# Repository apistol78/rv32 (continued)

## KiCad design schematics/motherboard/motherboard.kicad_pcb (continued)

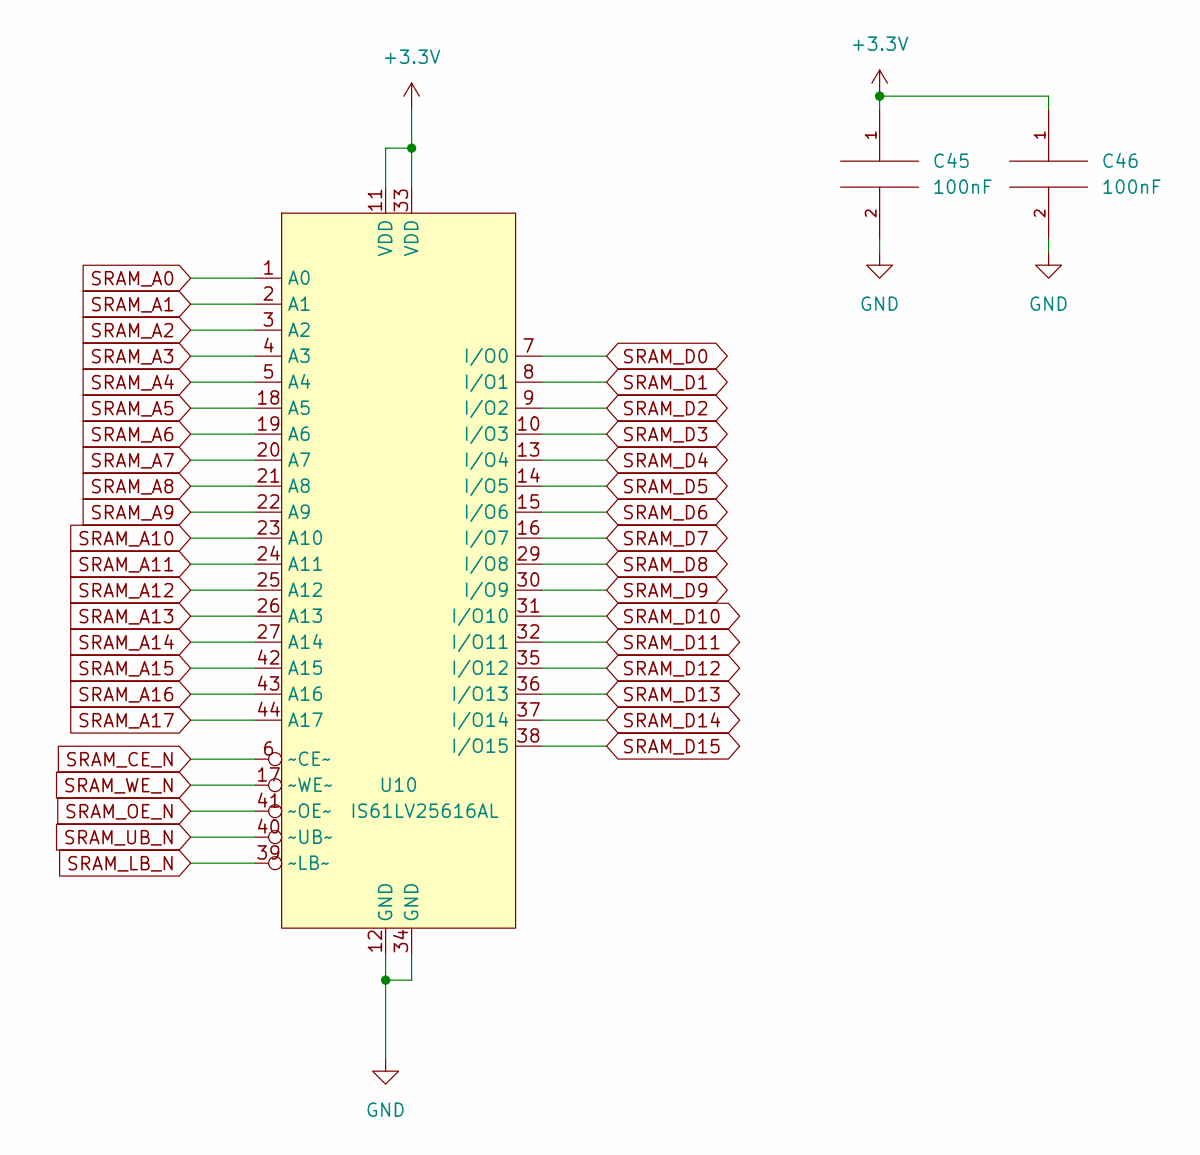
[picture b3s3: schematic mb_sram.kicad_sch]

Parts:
C45, C46: 100nF; C_0805_2012Metric_Pad1.18x1.45mm_HandSolder
U10: IS61LV25616AL; TSOP-II-44_10.16x18.41mm_P0.8mm

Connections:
+3V3: C45.1, C46.1, U10.11 (VDD), U10.33 (VDD); also elsewhere on the board
GND: C45.2, C46.2, U10.12 (GND), U10.34 (GND); also elsewhere on the board
SRAM_A0: U10.1 (A0); also elsewhere on the board
SRAM_A1: U10.2 (A1); also elsewhere on the board
SRAM_A2: U10.3 (A2); also elsewhere on the board
SRAM_A3: U10.4 (A3); also elsewhere on the board
SRAM_A4: U10.5 (A4); also elsewhere on the board
SRAM_A5: U10.18 (A5); also elsewhere on the board
SRAM_A6: U10.19 (A6); also elsewhere on the board
SRAM_A7: U10.20 (A7); also elsewhere on the board
SRAM_A8: U10.21 (A8); also elsewhere on the board
SRAM_A9: U10.22 (A9); also elsewhere on the board
SRAM_A10: U10.23 (A10); also elsewhere on the board
SRAM_A11: U10.24 (A11); also elsewhere on the board
SRAM_A12: U10.25 (A12); also elsewhere on the board
SRAM_A13: U10.26 (A13); also elsewhere on the board
SRAM_A14: U10.27 (A14); also elsewhere on the board
SRAM_A15: U10.42 (A15); also elsewhere on the board
SRAM_A16: U10.43 (A16); also elsewhere on the board
SRAM_A17: U10.44 (A17); also elsewhere on the board
SRAM_CE_N: U10.6 (~CE~); also elsewhere on the board
SRAM_D0: U10.7 (I/O0); also elsewhere on the board
SRAM_D1: U10.8 (I/O1); also elsewhere on the board
SRAM_D2: U10.9 (I/O2); also elsewhere on the board
SRAM_D3: U10.10 (I/O3); also elsewhere on the board
SRAM_D4: U10.13 (I/O4); also elsewhere on the board
SRAM_D5: U10.14 (I/O5); also elsewhere on the board
SRAM_D6: U10.15 (I/O6); also elsewhere on the board
SRAM_D7: U10.16 (I/O7); also elsewhere on the board
SRAM_D8: U10.29 (I/O8); also elsewhere on the board
SRAM_D9: U10.30 (I/O9); also elsewhere on the board
SRAM_D10: U10.31 (I/O10); also elsewhere on the board
SRAM_D11: U10.32 (I/O11); also elsewhere on the board
SRAM_D12: U10.35 (I/O12); also elsewhere on the board
SRAM_D13: U10.36 (I/O13); also elsewhere on the board
SRAM_D14: U10.37 (I/O14); also elsewhere on the board
SRAM_D15: U10.38 (I/O15); also elsewhere on the board
SRAM_LB_N: U10.39 (~LB~); also elsewhere on the board
SRAM_OE_N: U10.41 (~OE~); also elsewhere on the board
SRAM_UB_N: U10.40 (~UB~); also elsewhere on the board
SRAM_WE_N: U10.17 (~WE~); also elsewhere on the board

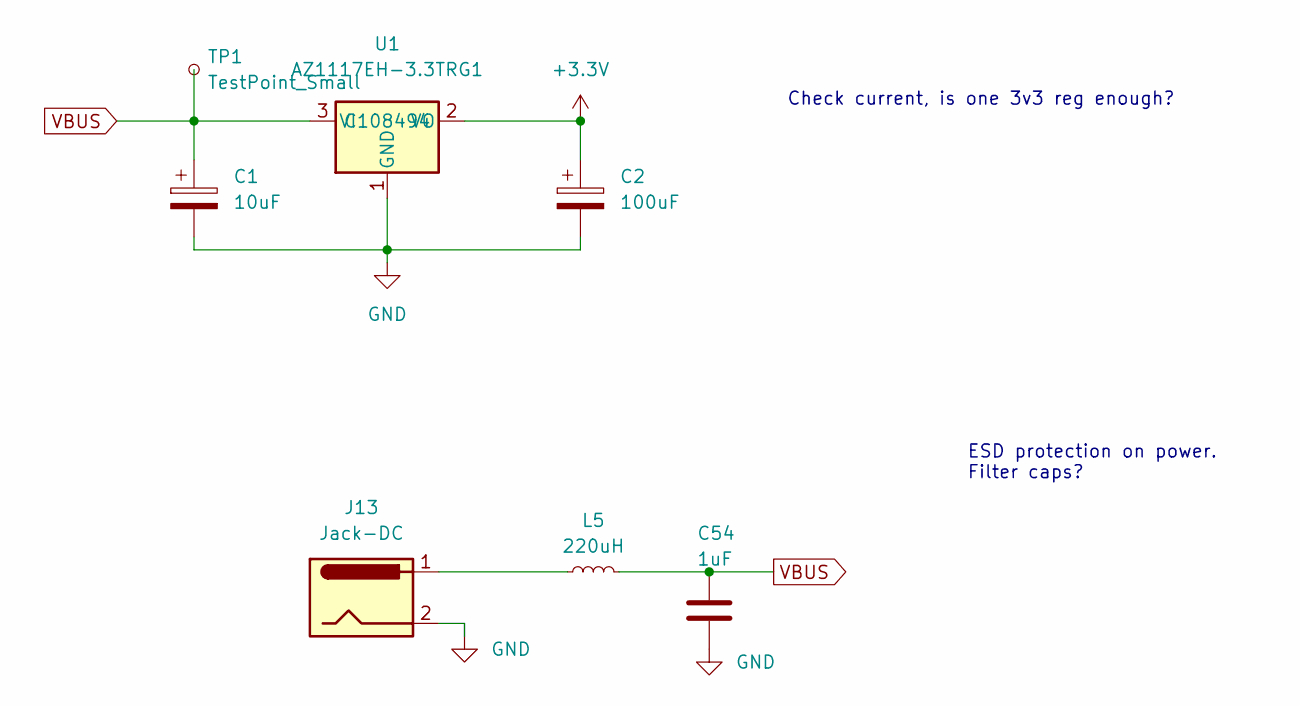
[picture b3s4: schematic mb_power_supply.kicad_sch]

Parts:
C1: 10uF; CP_Elec_5x5.3
C2: 100uF; CP_Elec_5x5.3
C54: 1uF; C_0805_2012Metric_Pad1.18x1.45mm_HandSolder
J13: Jack-DC; BarrelJack_CLIFF_FC681465S_SMT_Horizontal
L5: 220uH; L_0805_2012Metric
TP1: TestPoint_Small; TestPoint_Pad_D1.5mm
U1: AZ1117EH-3.3TRG1; SOT-223-3_TabPin2; LCSC C108494

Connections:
+3V3: C2.1, U1.2 (VO); also elsewhere on the board
GND: C1.2, C2.2, C54.2, J13.2, U1.1 (GND); also elsewhere on the board
unnamed: J13.1, L5.1
VBUS: C1.1, C54.1, L5.2, TP1.1, U1.3 (VI); also elsewhere on the board

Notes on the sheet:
Check current, is one 3v3 reg enough?
ESD protection on power. Filter caps?

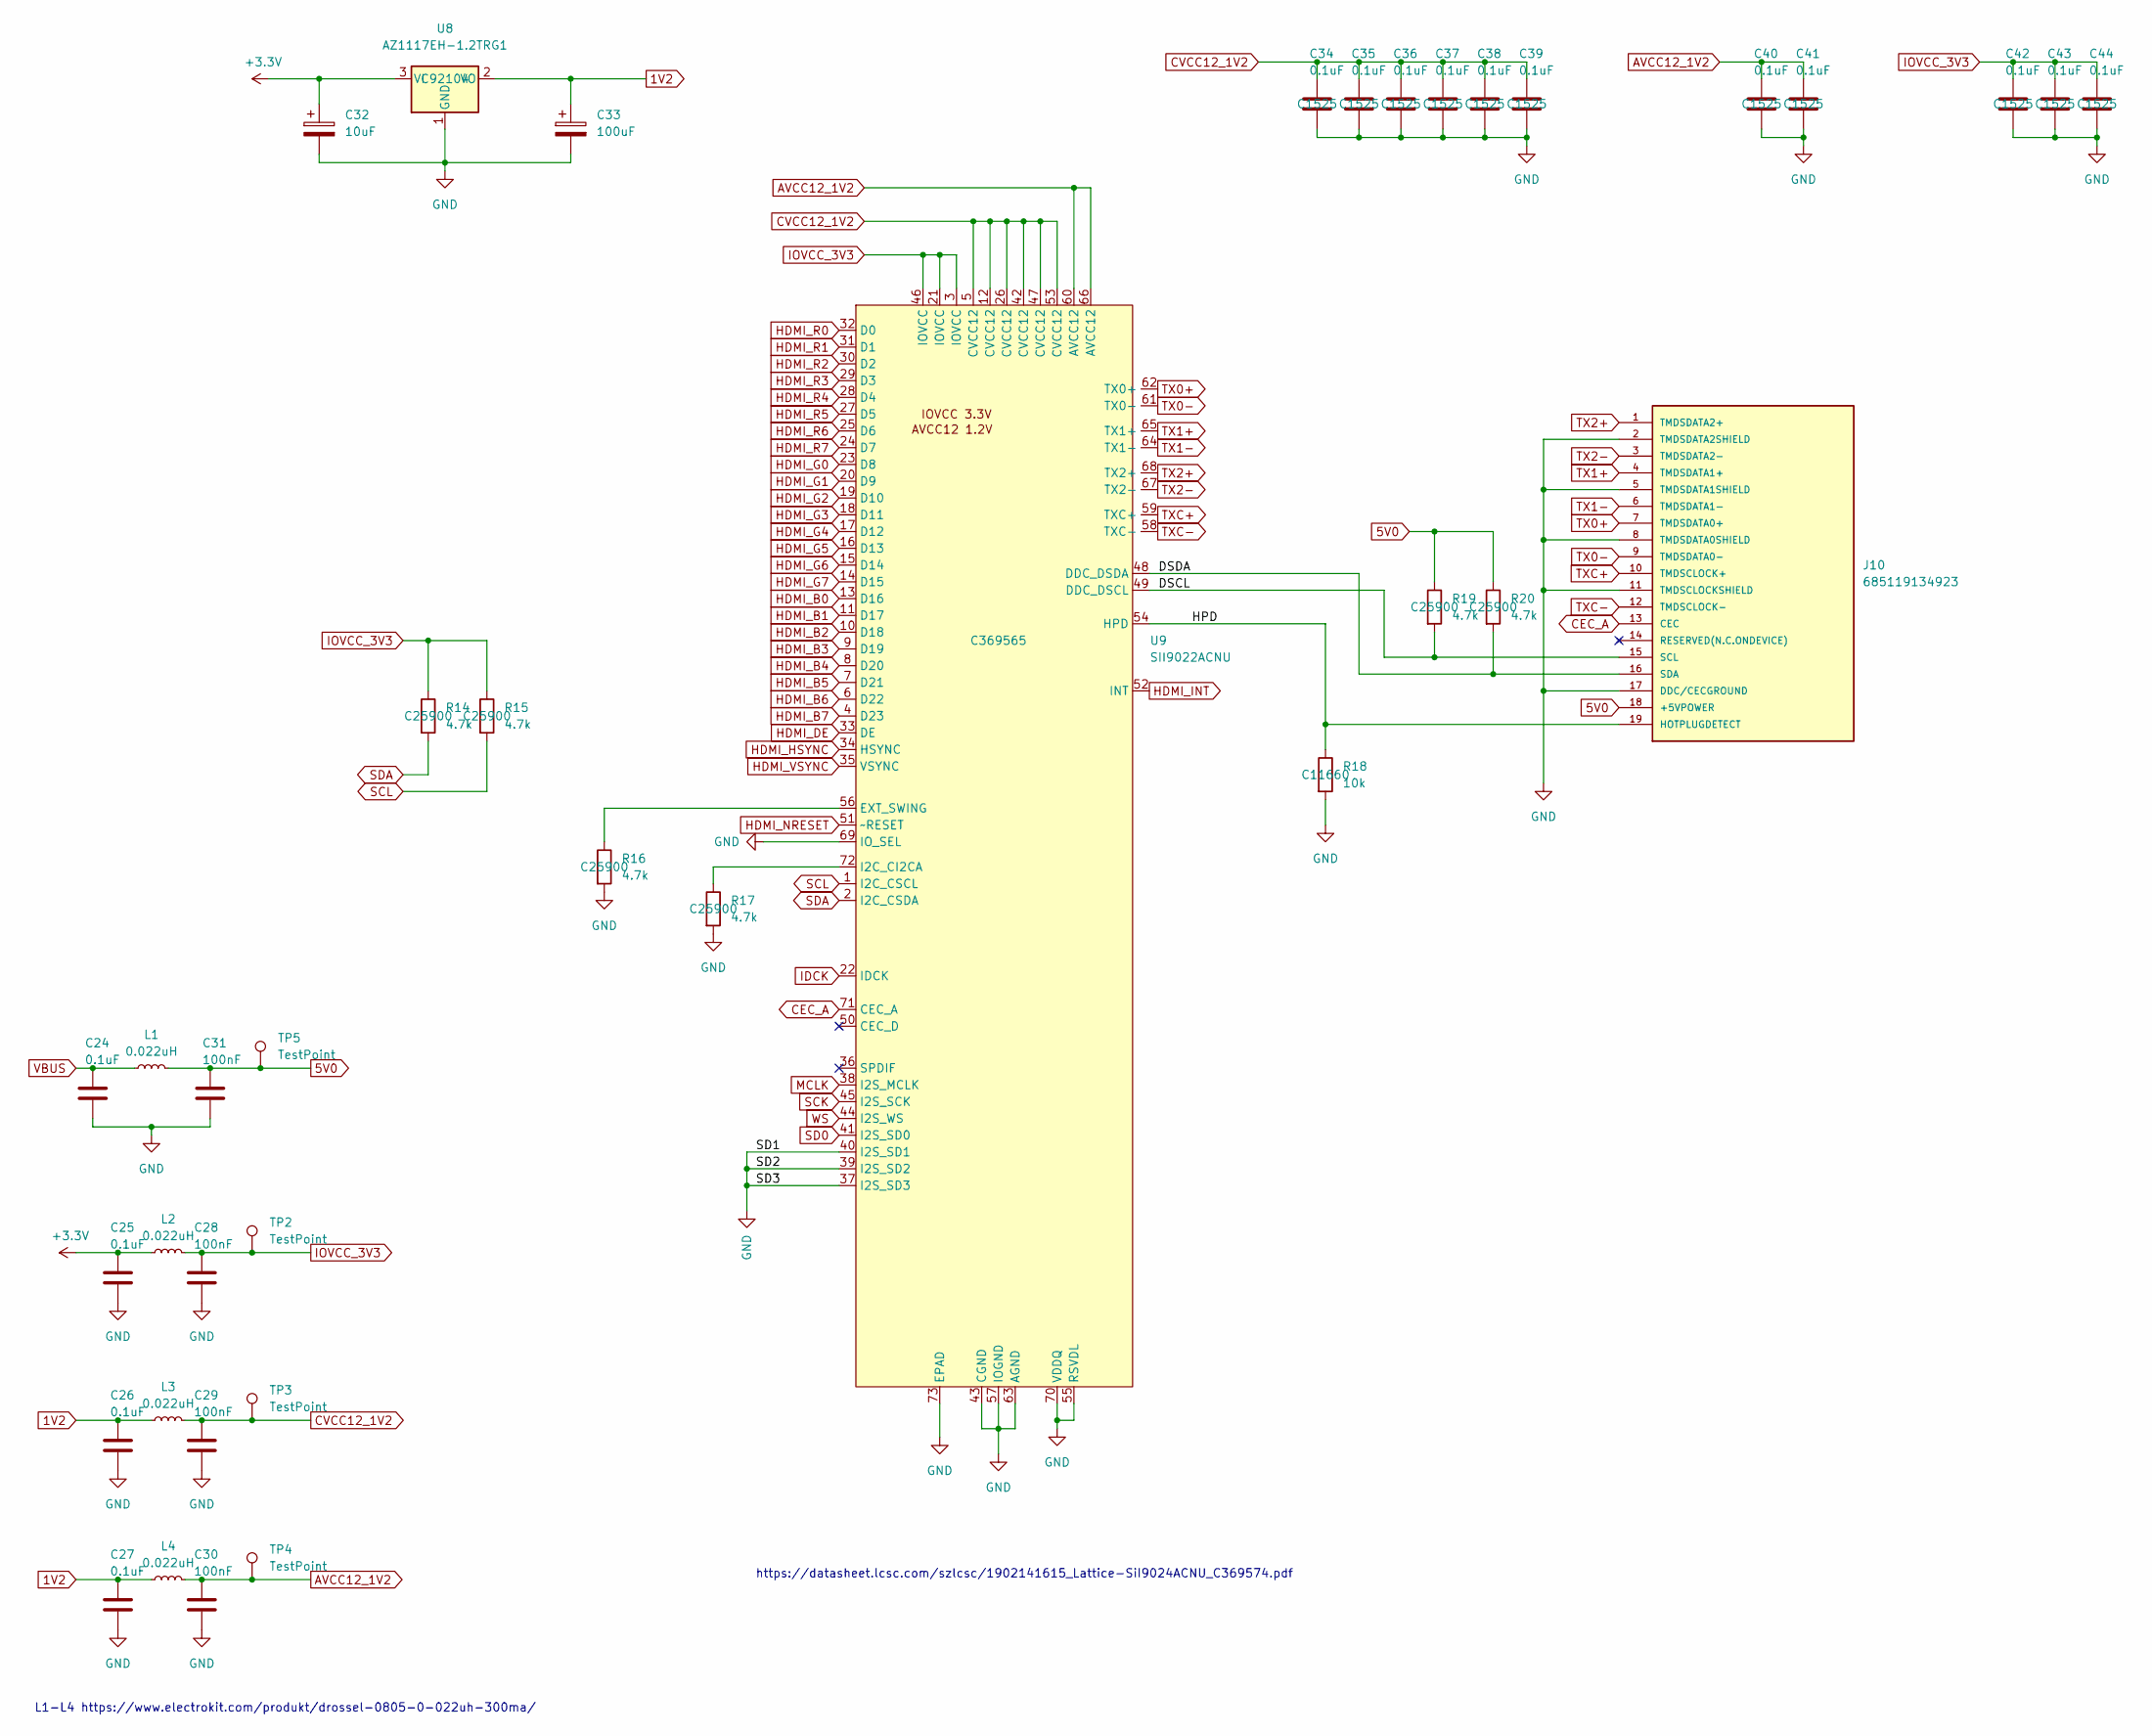
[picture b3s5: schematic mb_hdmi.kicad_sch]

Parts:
C24, C25, C26, C27: 0.1uF; C_0805_2012Metric_Pad1.18x1.45mm_HandSolder
C28, C29, C30, C31: 100nF; C_0805_2012Metric_Pad1.18x1.45mm_HandSolder
C32: 10uF; CP_Elec_5x5.3
C33: 100uF; CP_Elec_5x5.3
C34, C35, C36, C37, C38, C39, C40, C41, C42, C43, C44: 0.1uF; C_0402_1005Metric; LCSC C1525
J10: 685119134923; LCSC C720616
L1: 0.022uH; L_0805_2012Metric_Pad1.05x1.20mm_HandSolder
L2, L3, L4: 0.022uH; L_0805_2012Metric_Pad1.15x1.40mm_HandSolder
R14, R15, R16, R17, R19, R20: 4.7k; R_0402_1005Metric; LCSC C25900
R18: 10k; R_0402_1005Metric; LCSC C11660
TP2, TP3, TP4, TP5: TestPoint; TestPoint_Pad_D1.0mm
U8: AZ1117EH-1.2TRG1; SOT-223-3_TabPin2; LCSC C92104
U9: SII9022ACNU; QFN-72-1EP_10x10mm_P0.5mm_EP6x6mm; LCSC C369565

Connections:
1V2: C26.1, C27.1, C33.1, L3.1, L4.1, U8.2 (VO)
5V0: C31.1, J10.18 (+5VPOWER), L1.2, R19.1, R20.1, TP5.1
+3V3: C25.1, C32.1, L2.1, U8.3 (VI); also elsewhere on the board
/HDMI/DSCL: J10.15 (SCL), R19.2, U9.49 (DDC_DSCL)
/HDMI/DSDA: J10.16 (SDA), R20.2, U9.48 (DDC_DSDA)
/HDMI/HPD: J10.19 (HOTPLUGDETECT), R18.1, U9.54 (HPD)
AVCC12_1V2: C30.1, C40.1, C41.1, L4.2, TP4.1, U9.60 (AVCC12), U9.66 (AVCC12)
CEC_A: J10.13 (CEC), U9.71 (CEC_A)
CVCC12_1V2: C29.1, C34.1, C35.1, C36.1, C37.1, C38.1, C39.1, L3.2, TP3.1, U9.5 (CVCC12), U9.12 (CVCC12), U9.26 (CVCC12), U9.42 (CVCC12), U9.47 (CVCC12), U9.53 (CVCC12)
GND: C24.2, C25.2, C26.2, C27.2, C28.2, C29.2, C30.2, C31.2, C32.2, C33.2, C34.2, C35.2, C36.2, C37.2, C38.2, C39.2, C40.2, C41.2, C42.2, C43.2, C44.2, J10.2 (TMDSDATA2SHIELD), J10.5 (TMDSDATA1SHIELD), J10.8 (TMDSDATA0SHIELD), J10.11 (TMDSCLOCKSHIELD), J10.17 (DDC/CECGROUND), R16.2, R17.2, R18.2, U8.1 (GND), U9.37 (I2S_SD3), U9.39 (I2S_SD2), U9.40 (I2S_SD1), U9.43 (CGND), U9.55 (RSVDL), U9.57 (IOGND), U9.63 (AGND), U9.69 (IO_SEL), U9.70 (VDDQ), U9.73 (EPAD); also elsewhere on the board
HDMI_B0: U9.13 (D16); also elsewhere on the board
HDMI_B1: U9.11 (D17); also elsewhere on the board
HDMI_B2: U9.10 (D18); also elsewhere on the board
HDMI_B3: U9.9 (D19); also elsewhere on the board
HDMI_B4: U9.8 (D20); also elsewhere on the board
HDMI_B5: U9.7 (D21); also elsewhere on the board
HDMI_B6: U9.6 (D22); also elsewhere on the board
HDMI_B7: U9.4 (D23); also elsewhere on the board
HDMI_DE: U9.33 (DE); also elsewhere on the board
HDMI_G0: U9.23 (D8); also elsewhere on the board
HDMI_G1: U9.20 (D9); also elsewhere on the board
HDMI_G2: U9.19 (D10); also elsewhere on the board
HDMI_G3: U9.18 (D11); also elsewhere on the board
HDMI_G4: U9.17 (D12); also elsewhere on the board
HDMI_G5: U9.16 (D13); also elsewhere on the board
HDMI_G6: U9.15 (D14); also elsewhere on the board
HDMI_G7: U9.14 (D15); also elsewhere on the board
HDMI_HSYNC: U9.34 (HSYNC); also elsewhere on the board
HDMI_INT: U9.52 (INT); also elsewhere on the board
HDMI_NRESET: U9.51 (~RESET); also elsewhere on the board
HDMI_R0: U9.32 (D0); also elsewhere on the board
HDMI_R1: U9.31 (D1); also elsewhere on the board
HDMI_R2: U9.30 (D2); also elsewhere on the board
HDMI_R3: U9.29 (D3); also elsewhere on the board
HDMI_R4: U9.28 (D4); also elsewhere on the board
HDMI_R5: U9.27 (D5); also elsewhere on the board
HDMI_R6: U9.25 (D6); also elsewhere on the board
HDMI_R7: U9.24 (D7); also elsewhere on the board
HDMI_VSYNC: U9.35 (VSYNC); also elsewhere on the board
IDCK: U9.22 (IDCK); also elsewhere on the board
IOVCC_3V3: C28.1, C42.1, C43.1, C44.1, L2.2, R14.1, R15.1, TP2.1, U9.3 (IOVCC), U9.21 (IOVCC), U9.46 (IOVCC)
MCLK: U9.38 (I2S_MCLK); also elsewhere on the board
unnamed: R16.1, U9.56 (EXT_SWING)
unnamed: R17.1, U9.72 (I2C_CI2CA)
SCK: U9.45 (I2S_SCK); also elsewhere on the board
SCL: R15.2, U9.1 (I2C_CSCL); also elsewhere on the board
SD0: U9.41 (I2S_SD0); also elsewhere on the board
SDA: R14.2, U9.2 (I2C_CSDA); also elsewhere on the board
TX0+: J10.7 (TMDSDATA0+), U9.62 (TX0+)
TX0-: J10.9 (TMDSDATA0-), U9.61 (TX0-)
TX1+: J10.4 (TMDSDATA1+), U9.65 (TX1+)
TX1-: J10.6 (TMDSDATA1-), U9.64 (TX1-)
TX2+: J10.1 (TMDSDATA2+), U9.68 (TX2+)
TX2-: J10.3 (TMDSDATA2-), U9.67 (TX2-)
TXC+: J10.10 (TMDSCLOCK+), U9.59 (TXC+)
TXC-: J10.12 (TMDSCLOCK-), U9.58 (TXC-)
VBUS: C24.1, L1.1; also elsewhere on the board
WS: U9.44 (I2S_WS); also elsewhere on the board

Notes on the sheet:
L1-L4 https://www.electrokit.com/produkt/drossel-0805-0-022uh-300ma/
https://datasheet.lcsc.com/szlcsc/1902141615_Lattice-SiI9024ACNU_C369574.pdf

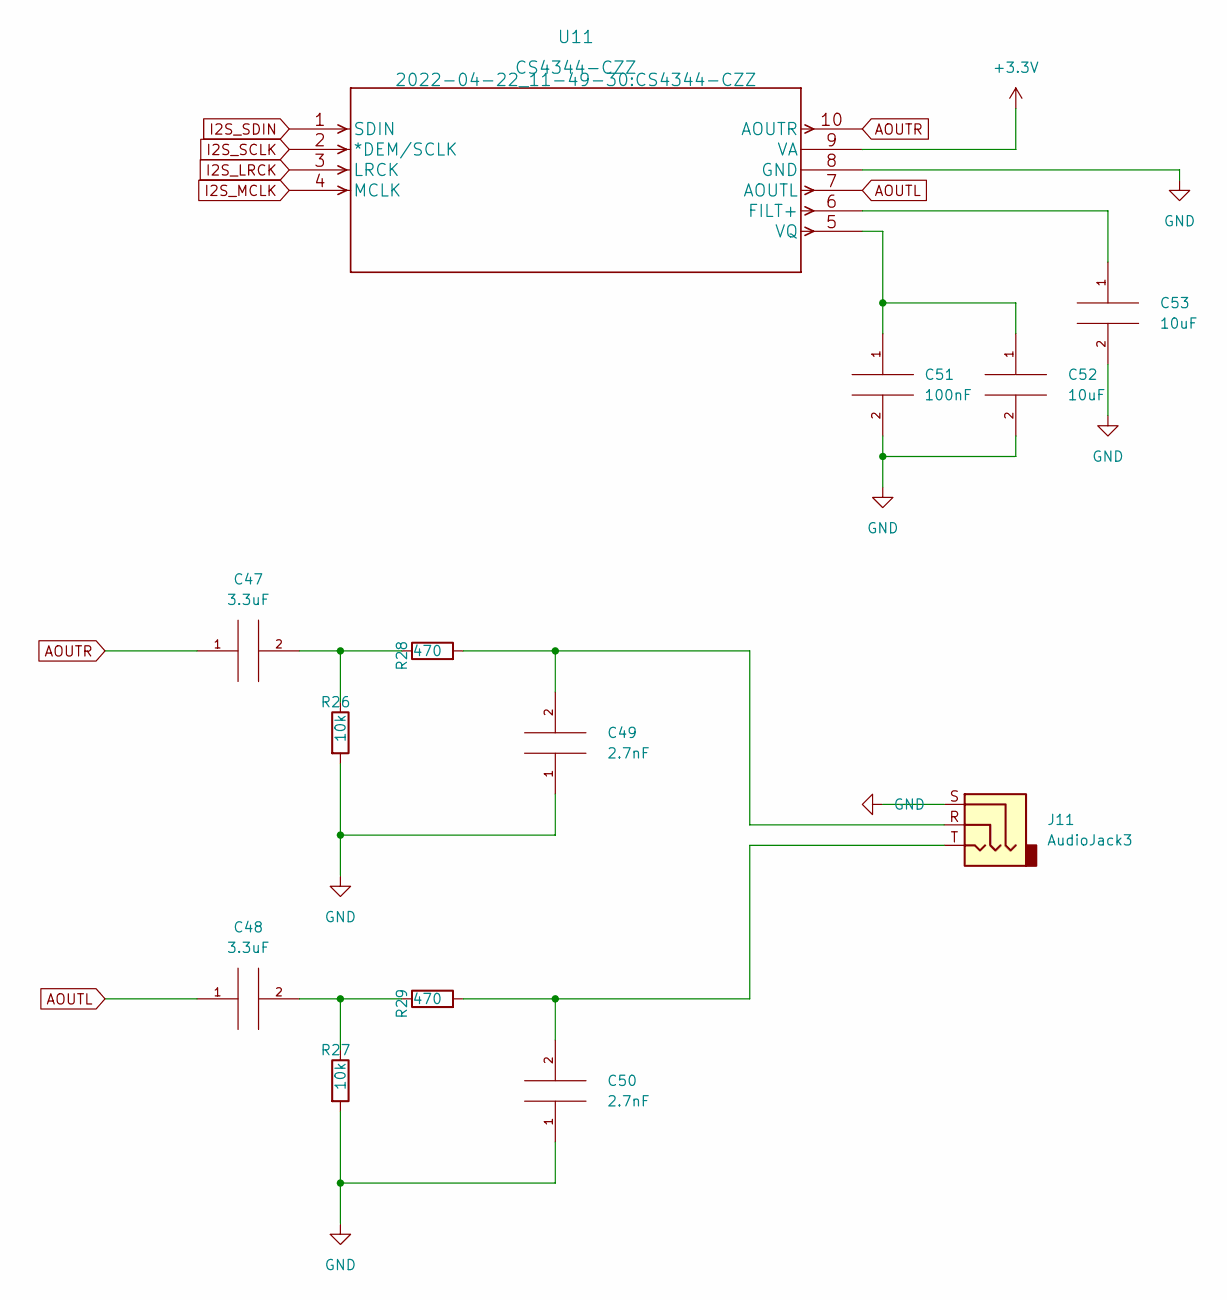
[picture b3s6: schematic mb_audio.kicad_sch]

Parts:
C47, C48: 3.3uF; C_0805_2012Metric_Pad1.18x1.45mm_HandSolder
C49, C50: 2.7nF; C_0805_2012Metric_Pad1.18x1.45mm_HandSolder
C51: 100nF; C_0805_2012Metric_Pad1.18x1.45mm_HandSolder
C52, C53: 10uF; C_0805_2012Metric_Pad1.18x1.45mm_HandSolder
J11: AudioJack3; Jack_3.5mm_CUI_SJ-3523-SMT_Horizontal
R26, R27: 10k; R_0805_2012Metric_Pad1.20x1.40mm_HandSolder
R28, R29: 470; R_0805_2012Metric_Pad1.20x1.40mm_HandSolder
U11: CS4344-CZZ

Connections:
+3V3: U11.9 (VA); also elsewhere on the board
AOUTL: C48.1, U11.7 (AOUTL)
AOUTR: C47.1, U11.10 (AOUTR)
GND: C49.1, C50.1, C51.2, C52.2, C53.2, J11.S, R26.2, R27.2, U11.8 (GND); also elsewhere on the board
I2S_LRCK: U11.3 (LRCK)
I2S_MCLK: U11.4 (MCLK)
I2S_SCLK: U11.2 (*DEM/SCLK)
I2S_SDIN: U11.1 (SDIN)
unnamed: C47.2, R26.1, R28.1
unnamed: C48.2, R27.1, R29.1
unnamed: C49.2, J11.R, R28.2
unnamed: C50.2, J11.T, R29.2
unnamed: C51.1, C52.1, U11.5 (VQ)
unnamed: C53.1, U11.6 (FILT+)

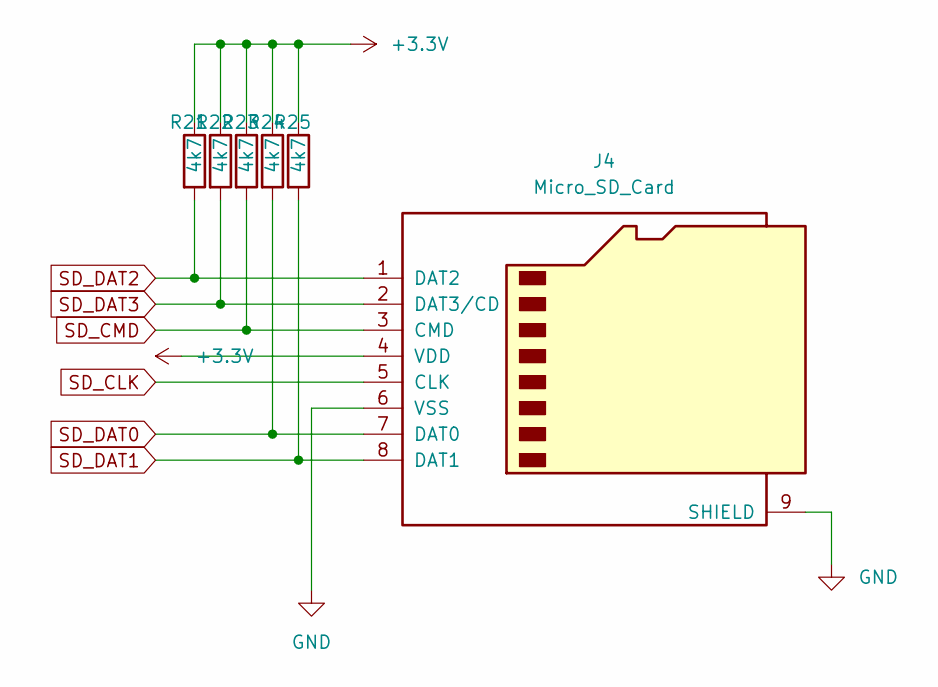
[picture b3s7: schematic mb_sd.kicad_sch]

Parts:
J4: Micro_SD_Card; microSD_HC_Hirose_DM3D-SF
R21, R22, R23, R24, R25: 4k7; R_0805_2012Metric_Pad1.20x1.40mm_HandSolder

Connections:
+3V3: J4.4 (VDD), R21.1, R22.1, R23.1, R24.1, R25.1; also elsewhere on the board
GND: J4.6 (VSS), J4.9 (SHIELD); also elsewhere on the board
SD_CLK: J4.5 (CLK); also elsewhere on the board
SD_CMD: J4.3 (CMD), R23.2; also elsewhere on the board
SD_DAT0: J4.7 (DAT0), R24.2; also elsewhere on the board
SD_DAT1: J4.8 (DAT1), R25.2; also elsewhere on the board
SD_DAT2: J4.1 (DAT2), R21.2; also elsewhere on the board
SD_DAT3: J4.2 (DAT3/CD), R22.2; also elsewhere on the board

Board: 4 copper layers, 126 parts (0 on the bottom side), 160 nets, no tracks yet.

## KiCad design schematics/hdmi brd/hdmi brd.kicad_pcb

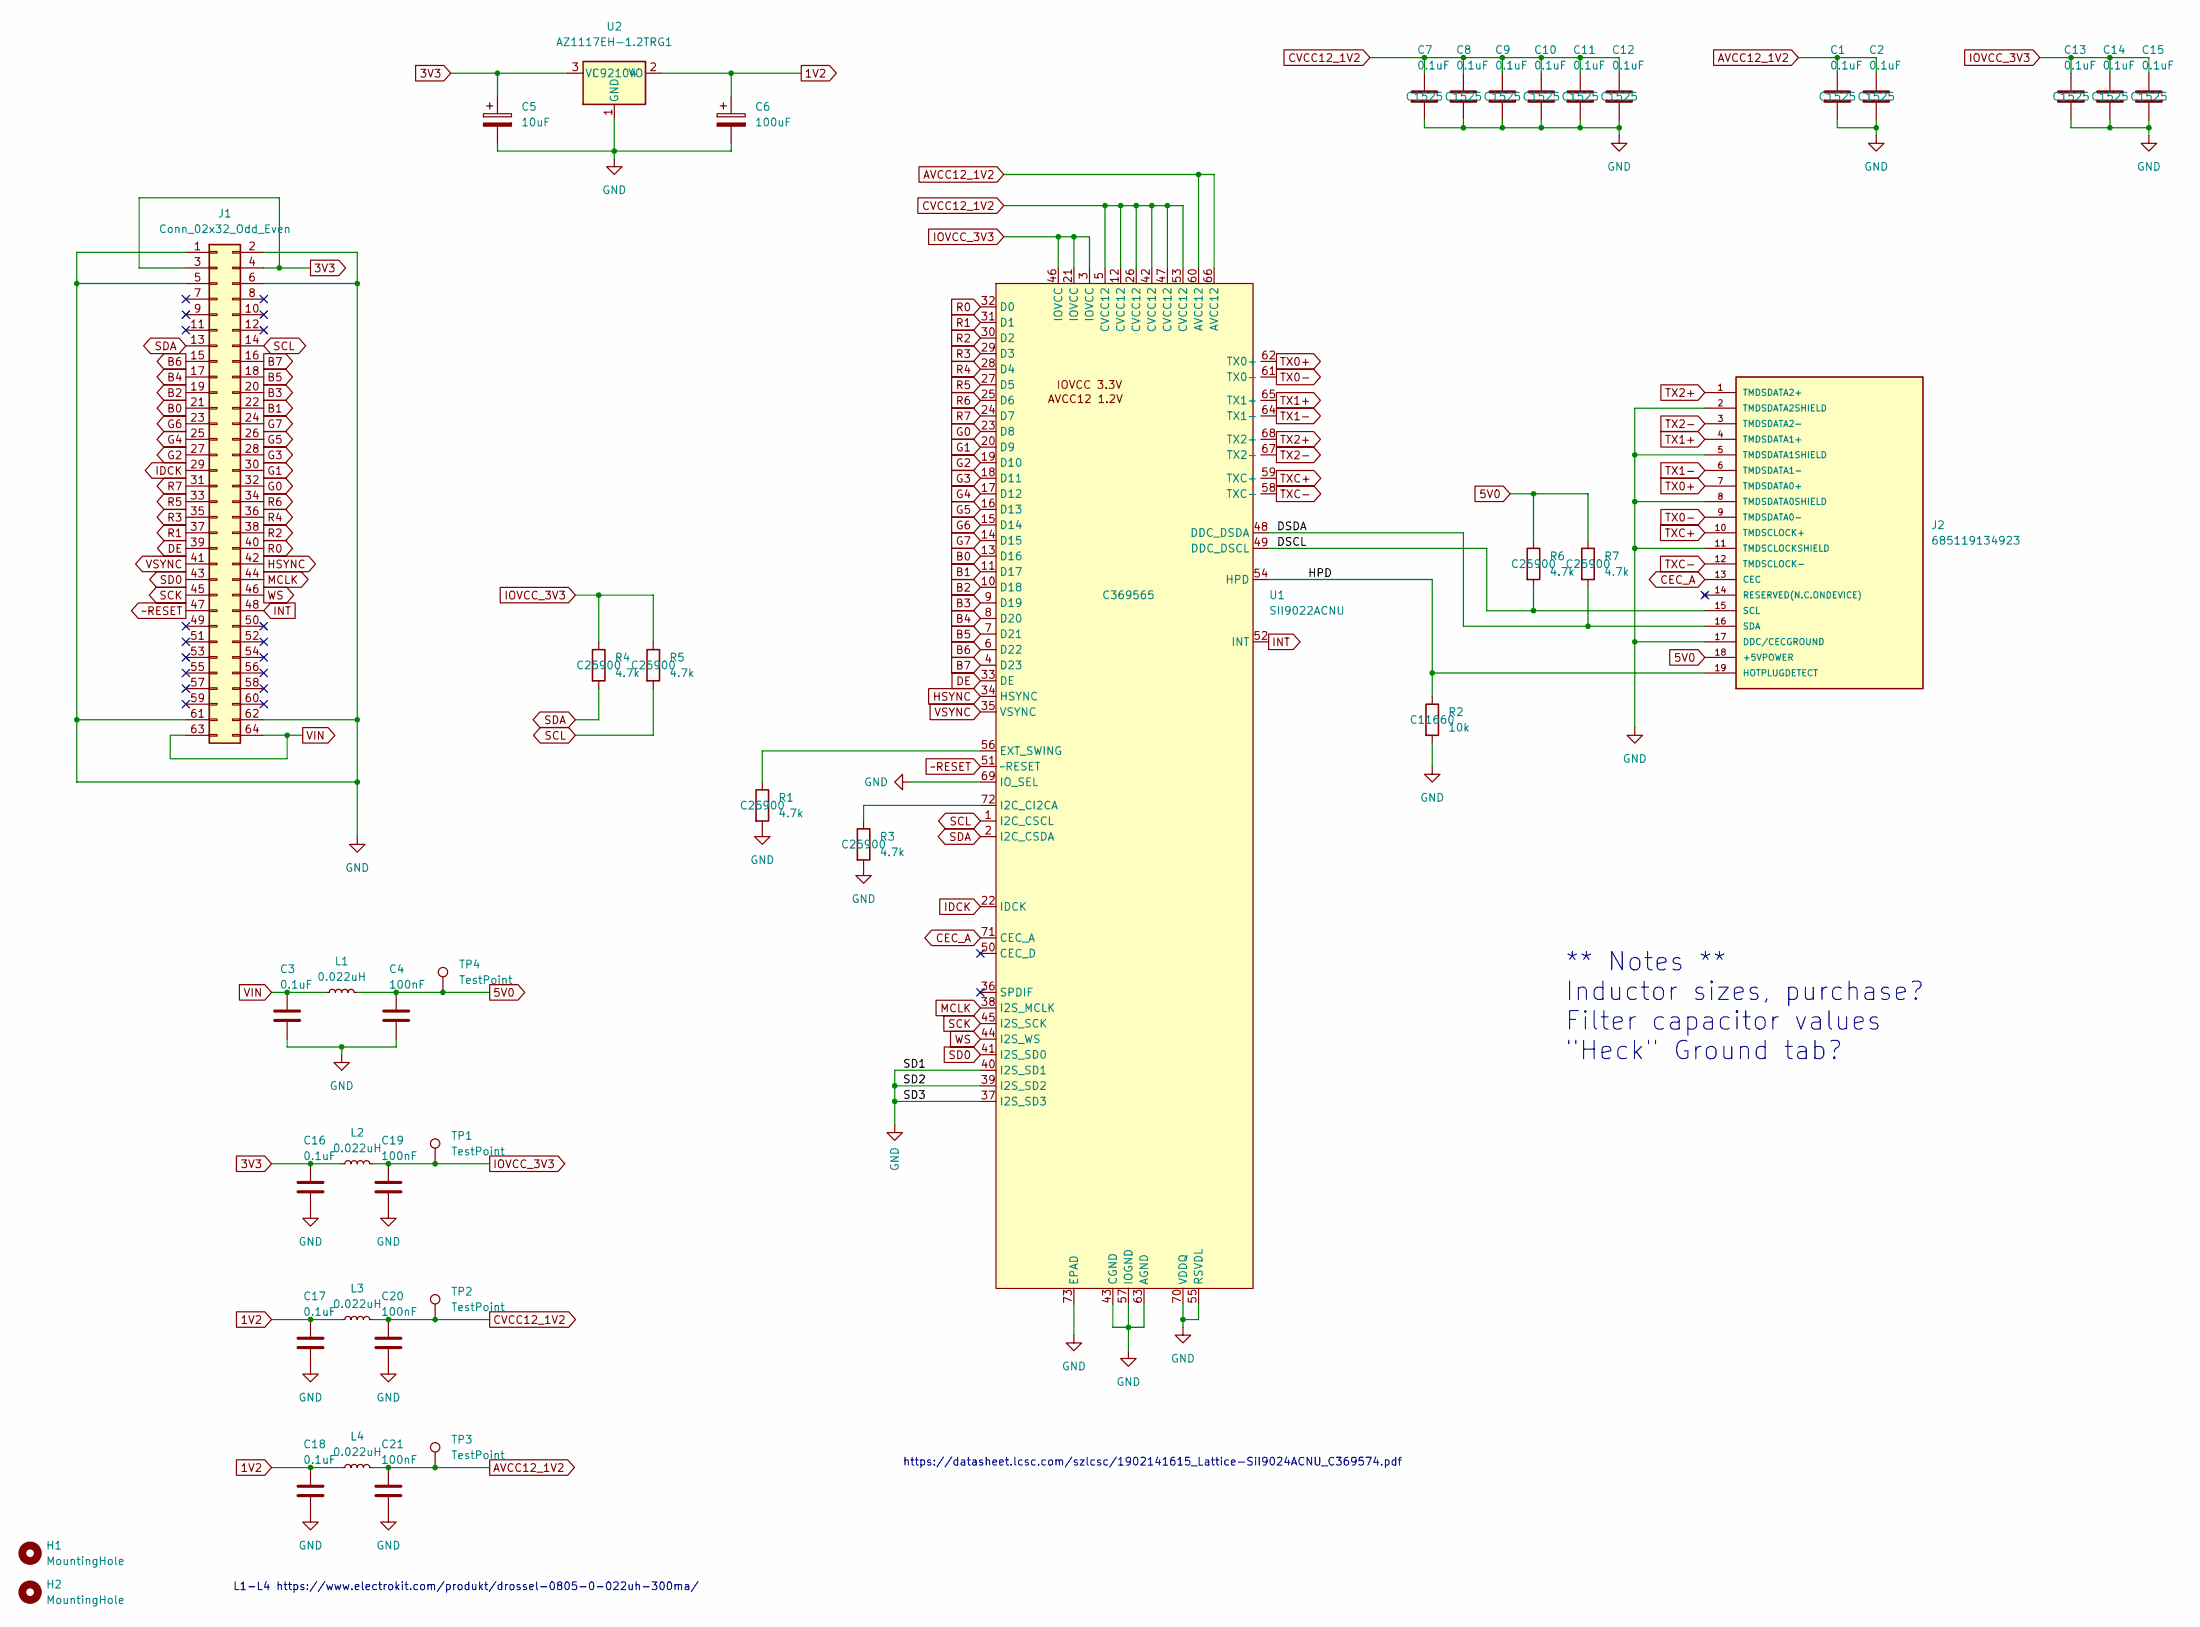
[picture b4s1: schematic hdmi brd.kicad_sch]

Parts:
C1, C2, C7, C8, C9, C10, C11, C12, C13, C14, C15: 0.1uF; C_0402_1005Metric; LCSC C1525
C3, C16, C17, C18: 0.1uF; C_0805_2012Metric_Pad1.18x1.45mm_HandSolder
C4, C19, C20, C21: 100nF; C_0805_2012Metric_Pad1.18x1.45mm_HandSolder
C5: 10uF; CP_Elec_5x5.3
C6: 100uF; CP_Elec_5x5.3
H1, H2: MountingHole; MountingHole_3.2mm_M3_DIN965_Pad
J1: Conn_02x32_Odd_Even; PinSocket_2x32_P2.54mm_Vertical
J2: 685119134923; LCSC C720616
L1: 0.022uH; L_0805_2012Metric_Pad1.05x1.20mm_HandSolder
L2, L3, L4: 0.022uH; L_0805_2012Metric_Pad1.15x1.40mm_HandSolder
R1, R3, R4, R5, R6, R7: 4.7k; R_0402_1005Metric; LCSC C25900
R2: 10k; R_0402_1005Metric; LCSC C11660
TP1, TP2, TP3, TP4: TestPoint; TestPoint_Pad_D1.0mm
U1: SII9022ACNU; QFN-72-1EP_10x10mm_P0.5mm_EP6x6mm; LCSC C369565
U2: AZ1117EH-1.2TRG1; SOT-223-3_TabPin2; LCSC C92104

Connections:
1V2: C6.1, C17.1, C18.1, L3.1, L4.1, U2.2 (VO)
3V3: C5.1, C16.1, J1.3, J1.4, L2.1, U2.3 (VI)
5V0: C4.1, J2.18 (+5VPOWER), L1.2, R6.1, R7.1, TP4.1
/DSCL: J2.15 (SCL), R6.2, U1.49 (DDC_DSCL)
/DSDA: J2.16 (SDA), R7.2, U1.48 (DDC_DSDA)
/HPD: J2.19 (HOTPLUGDETECT), R2.1, U1.54 (HPD)
AVCC12_1V2: C1.1, C2.1, C21.1, L4.2, TP3.1, U1.60 (AVCC12), U1.66 (AVCC12)
B0: J1.21, U1.13 (D16)
B1: J1.22, U1.11 (D17)
B2: J1.19, U1.10 (D18)
B3: J1.20, U1.9 (D19)
B4: J1.17, U1.8 (D20)
B5: J1.18, U1.7 (D21)
B6: J1.15, U1.6 (D22)
B7: J1.16, U1.4 (D23)
CEC_A: J2.13 (CEC), U1.71 (CEC_A)
CVCC12_1V2: C7.1, C8.1, C9.1, C10.1, C11.1, C12.1, C20.1, L3.2, TP2.1, U1.5 (CVCC12), U1.12 (CVCC12), U1.26 (CVCC12), U1.42 (CVCC12), U1.47 (CVCC12), U1.53 (CVCC12)
DE: J1.39, U1.33 (DE)
G0: J1.32, U1.23 (D8)
G1: J1.30, U1.20 (D9)
G2: J1.27, U1.19 (D10)
G3: J1.28, U1.18 (D11)
G4: J1.25, U1.17 (D12)
G5: J1.26, U1.16 (D13)
G6: J1.23, U1.15 (D14)
G7: J1.24, U1.14 (D15)
GND: C1.2, C2.2, C3.2, C4.2, C5.2, C6.2, C7.2, C8.2, C9.2, C10.2, C11.2, C12.2, C13.2, C14.2, C15.2, C16.2, C17.2, C18.2, C19.2, C20.2, C21.2, J1.1, J1.2, J1.5, J1.6, J1.61, J1.62, J2.2 (TMDSDATA2SHIELD), J2.5 (TMDSDATA1SHIELD), J2.8 (TMDSDATA0SHIELD), J2.11 (TMDSCLOCKSHIELD), J2.17 (DDC/CECGROUND), R1.2, R2.2, R3.2, U1.37 (I2S_SD3), U1.39 (I2S_SD2), U1.40 (I2S_SD1), U1.43 (CGND), U1.55 (RSVDL), U1.57 (IOGND), U1.63 (AGND), U1.69 (IO_SEL), U1.70 (VDDQ), U1.73 (EPAD), U2.1 (GND)
HSYNC: J1.42, U1.34 (HSYNC)
IDCK: J1.29, U1.22 (IDCK)
INT: J1.48, U1.52 (INT)
IOVCC_3V3: C13.1, C14.1, C15.1, C19.1, L2.2, R4.1, R5.1, TP1.1, U1.3 (IOVCC), U1.21 (IOVCC), U1.46 (IOVCC)
MCLK: J1.44, U1.38 (I2S_MCLK)
unnamed: R1.1, U1.56 (EXT_SWING)
unnamed: R3.1, U1.72 (I2C_CI2CA)
R0: J1.40, U1.32 (D0)
R1: J1.37, U1.31 (D1)
R2: J1.38, U1.30 (D2)
R3: J1.35, U1.29 (D3)
R4: J1.36, U1.28 (D4)
R5: J1.33, U1.27 (D5)
R6: J1.34, U1.25 (D6)
R7: J1.31, U1.24 (D7)
SCK: J1.45, U1.45 (I2S_SCK)
SCL: J1.14, R5.2, U1.1 (I2C_CSCL)
SD0: J1.43, U1.41 (I2S_SD0)
SDA: J1.13, R4.2, U1.2 (I2C_CSDA)
TX0+: J2.7 (TMDSDATA0+), U1.62 (TX0+)
TX0-: J2.9 (TMDSDATA0-), U1.61 (TX0-)
TX1+: J2.4 (TMDSDATA1+), U1.65 (TX1+)
TX1-: J2.6 (TMDSDATA1-), U1.64 (TX1-)
TX2+: J2.1 (TMDSDATA2+), U1.68 (TX2+)
TX2-: J2.3 (TMDSDATA2-), U1.67 (TX2-)
TXC+: J2.10 (TMDSCLOCK+), U1.59 (TXC+)
TXC-: J2.12 (TMDSCLOCK-), U1.58 (TXC-)
VIN: C3.1, J1.63, J1.64, L1.1
VSYNC: J1.41, U1.35 (VSYNC)
WS: J1.46, U1.44 (I2S_WS)
~RESET: J1.47, U1.51 (~RESET)

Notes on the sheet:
L1-L4 https://www.electrokit.com/produkt/drossel-0805-0-022uh-300ma/
https://datasheet.lcsc.com/szlcsc/1902141615_Lattice-SiI9024ACNU_C369574.pdf
** Notes ** Inductor sizes, purchase? Filter capacitor values "Heck" Ground tab?

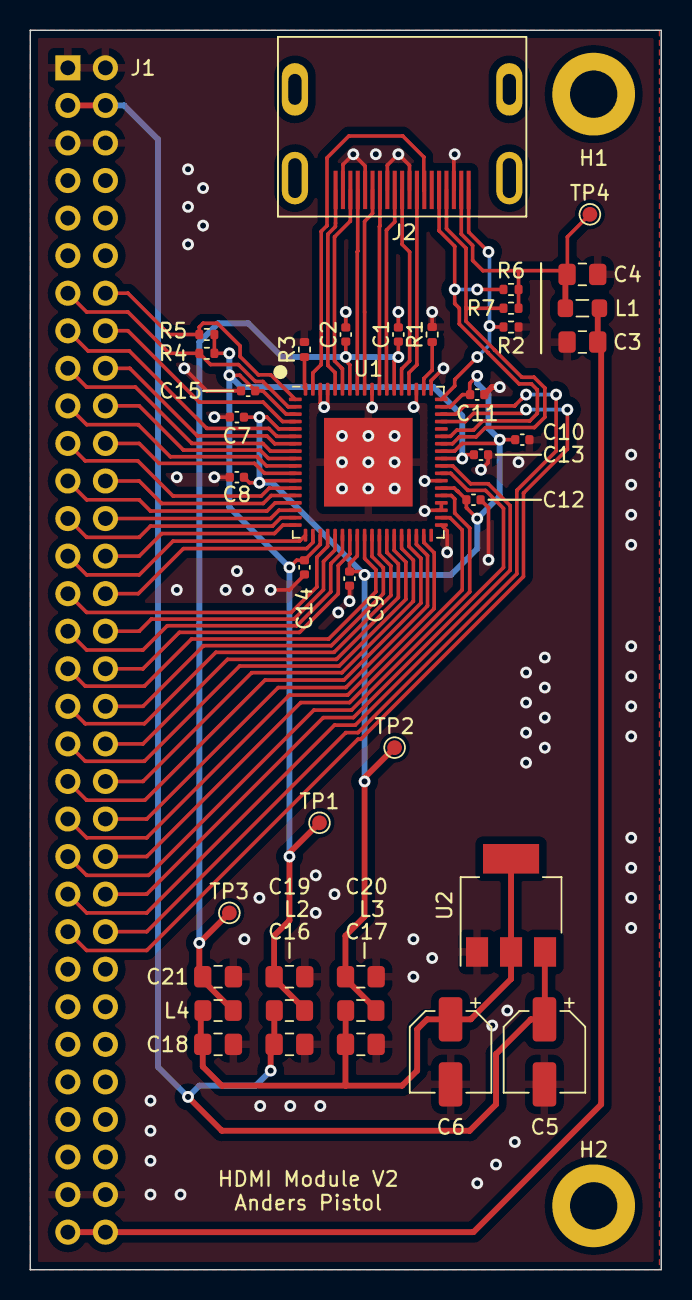
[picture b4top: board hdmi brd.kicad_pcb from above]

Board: 2 copper layers, 42.7 x 83.8 mm, 42 parts (1 on the bottom side), 58 nets.

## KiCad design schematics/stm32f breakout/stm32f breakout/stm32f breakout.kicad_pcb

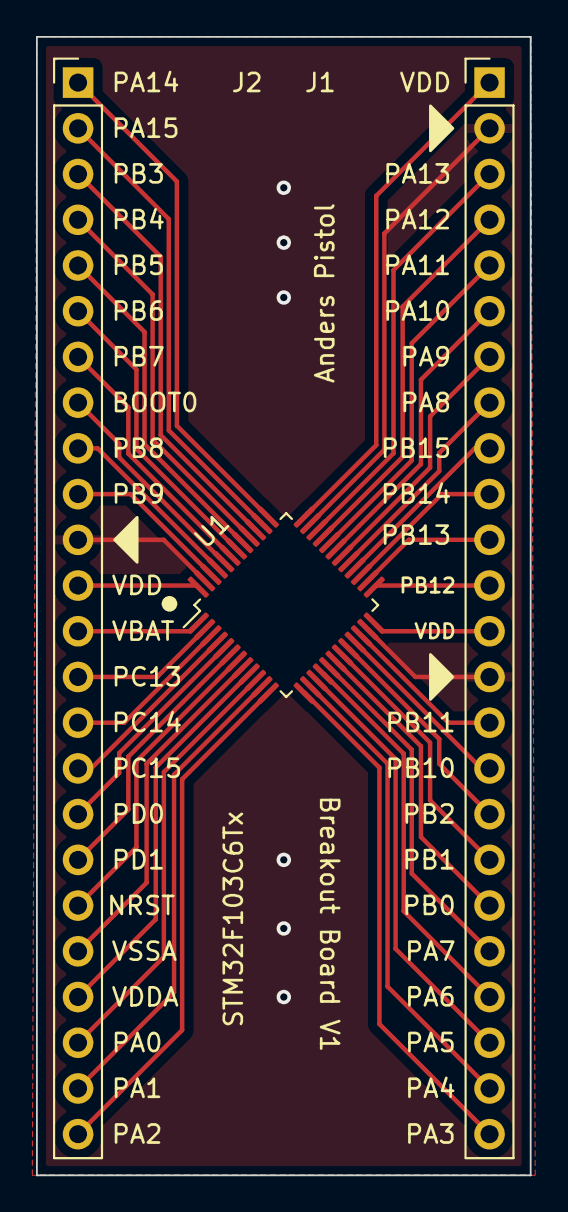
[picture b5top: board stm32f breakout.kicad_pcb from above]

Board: 2 copper layers, 27.4 x 63.2 mm, 3 parts (0 on the bottom side), 46 nets.

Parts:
J1, J2: Conn_01x24_Male; PinHeader_1x24_P2.54mm_Vertical
U1: STM32F103C6Tx; LQFP-48_7x7mm_P0.5mm

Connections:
GND: J1.2, J1.14, J2.11, U1.23 (VSS), U1.35 (VSS), U1.47 (VSS)
unnamed: J1.3, U1.34 (PA13)
unnamed: J1.4, U1.33 (PA12)
unnamed: J1.5, U1.32 (PA11)
unnamed: J1.12, U1.25 (PB12)
unnamed: J1.15, U1.22 (PB11)
unnamed: J1.16, U1.21 (PB10)
unnamed: J1.17, U1.20 (PB2)
unnamed: J1.18, U1.19 (PB1)
unnamed: J1.19, U1.18 (PB0)
unnamed: J2.5, U1.41 (PB5)
unnamed: J2.6, U1.42 (PB6)
unnamed: J2.7, U1.43 (PB7)
unnamed: J2.8, U1.44 (BOOT0)
unnamed: J2.9, U1.45 (PB8)
unnamed: J2.10, U1.46 (PB9)
unnamed: J2.12, U1.48 (VDD)
unnamed: J2.13, U1.1 (VBAT)
unnamed: J2.14, U1.2 (PC13)
unnamed: J2.15, U1.3 (PC14)
unnamed: J2.16, U1.4 (PC15)
unnamed: J2.17, U1.5 (PD0)
unnamed: J2.22, U1.10 (PA0)
unnamed: J2.23, U1.11 (PA1)
unnamed: J2.24, U1.12 (PA2)
unnamed: J2.18, U1.6 (PD1)
unnamed: J2.19, U1.7 (NRST)
unnamed: J2.20, U1.8 (VSSA)
unnamed: J2.21, U1.9 (VDDA)
unnamed: J1.24, U1.13 (PA3)
unnamed: J1.23, U1.14 (PA4)
unnamed: J1.22, U1.15 (PA5)
unnamed: J1.21, U1.16 (PA6)
unnamed: J1.20, U1.17 (PA7)
unnamed: J1.13, U1.24 (VDD)
unnamed: J1.11, U1.26 (PB13)
unnamed: J1.10, U1.27 (PB14)
unnamed: J1.9, U1.28 (PB15)
unnamed: J1.8, U1.29 (PA8)
unnamed: J1.7, U1.30 (PA9)
unnamed: J1.6, U1.31 (PA10)
unnamed: J1.1, U1.36 (VDD)
unnamed: J2.1, U1.37 (PA14)
unnamed: J2.2, U1.38 (PA15)
unnamed: J2.3, U1.39 (PB3)
unnamed: J2.4, U1.40 (PB4)
